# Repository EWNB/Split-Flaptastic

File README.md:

# Split-Flaptastic
Various files for making Split-Flap displays

# Files
* Circ/
  * Contains attempts and various circuit designs. [Here are lions](https://en.wikipedia.org/wiki/Here_be_dragons).
* Code/
  * Here lives embedded code for running split-flap devices or parts thereof.
  * RegFlap/ 
    * New Arduino shift register controlled split-flap display program.
  * RegSpinCTRL/
    * Old Arduino shift register controlled split-flap display program.
  * RegSpinFlap/
    * Arduino shift register controlled motor spinner for testing hardware.
* Flaps/
  * Within lies a script most reptilian that creates flap template PDFs.

# Blog
I write about this project on my blog. Search engines don't seem to know that it exists, so here's a link:
https://transistorized-tui.blogspot.com/search/label/Split-Flaptastic
These files on GitHub will likely be ahead of the narative on the blog, as I'm lazy and often prefer to advance the project than bother letting anybody know about it.

# Licence
Not sure yet...

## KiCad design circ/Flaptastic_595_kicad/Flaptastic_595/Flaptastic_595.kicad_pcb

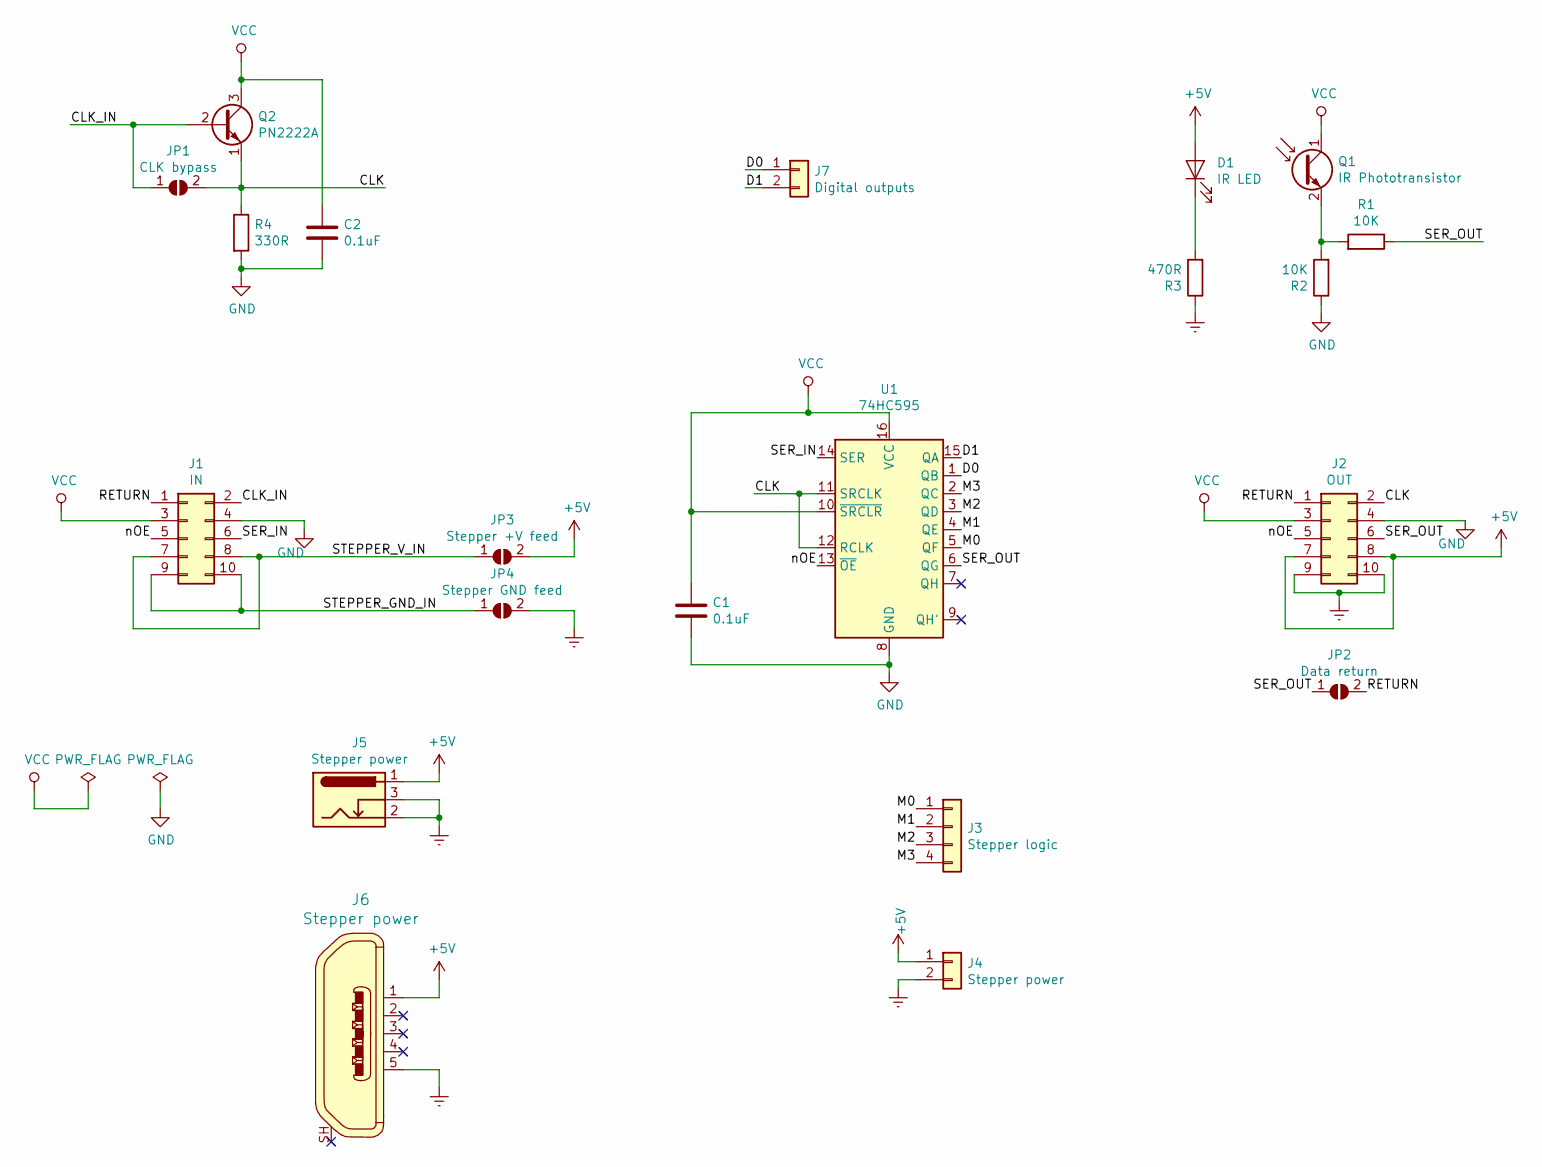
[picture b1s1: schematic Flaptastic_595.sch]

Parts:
C1, C2: 0.1uF; CAP-PTH-2.54
D1: IR LED; LED_D5.0mm_Clear
J1: IN; IDC-Header_2x05_P2.54mm_Vertical
J2: OUT; IDC-Header_2x05_P2.54mm_Vertical
J3: Stepper logic; PinHeader_1x04_P2.54mm_Vertical
J4: Stepper power; PinHeader_1x02_P2.54mm_Vertical
J5: Stepper power; BarrelJack_CUI_PJ-102AH_Horizontal
J6: Stepper power; USB_Micro_B_Female_10118194-0001LF; MPN 10118194-0001LF; Digi-Key_PN 609-4618-1-ND
J7: Digital outputs; PinHeader_1x02_P2.54mm_Vertical
JP1: CLK bypass; SolderJumper-2_P1.3mm_Open_RoundedPad1.0x1.5mm
JP2: Data return; SolderJumper-2_P1.3mm_Open_RoundedPad1.0x1.5mm
JP3: Stepper +V feed; SolderJumper-2_P1.3mm_Open_RoundedPad1.0x1.5mm
JP4: Stepper GND feed; SolderJumper-2_P1.3mm_Open_RoundedPad1.0x1.5mm
Q1: IR Phototransistor; LED_D5.0mm_IRBlack
Q2: PN2222A; TO-92_Inline
R1, R2: 10K; R_Axial_DIN0204_L3.6mm_D1.6mm_P7.62mm_Horizontal
R3: 470R; R_Axial_DIN0204_L3.6mm_D1.6mm_P7.62mm_Horizontal
R4: 330R; R_Axial_DIN0204_L3.6mm_D1.6mm_P7.62mm_Horizontal
U1: 74HC595; DIP-16_W7.62mm

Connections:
+5V: D1.2 (A), J2.7, J2.8, J4.1, J5.1, J6.1, JP3.2 (B)
/CLK: J2.2, JP1.2 (B), Q2.1 (E), R4.1, U1.11 (SRCLK), U1.12 (RCLK)
/CLK_IN: J1.2, JP1.1 (A), Q2.2 (B)
/D0: J7.1, U1.1 (QB)
/D1: J7.2, U1.15 (QA)
/M0: J3.1, U1.5 (QF)
/M1: J3.2, U1.4 (QE)
/M2: J3.3, U1.3 (QD)
/M3: J3.4, U1.2 (QC)
/RETURN: J1.1, J2.1, JP2.2 (B)
/SER_IN: J1.6, U1.14 (SER)
/SER_OUT: J2.6, JP2.1 (A), R1.1, U1.6 (QG)
/STEPPER_GND_IN: J1.9, J1.10, JP4.1 (A)
/STEPPER_V_IN: J1.7, J1.8, JP3.1 (A)
/nOE: J1.5, J2.5, U1.13 (~OE)
Earth: J2.9, J2.10, J4.2, J5.2, J5.3, J6.5, JP4.2 (B), R3.1
GND: C1.2, C2.2, J1.4, J2.4, R2.1, R4.2, U1.8 (GND)
unnamed: D1.1 (K), R3.2
unnamed: Q1.2 (E), R1.2, R2.2
VCC: C1.1, C2.1, J1.3, J2.3, Q1.1 (C), Q2.3 (C), U1.10 (~SRCLR), U1.16 (VCC)

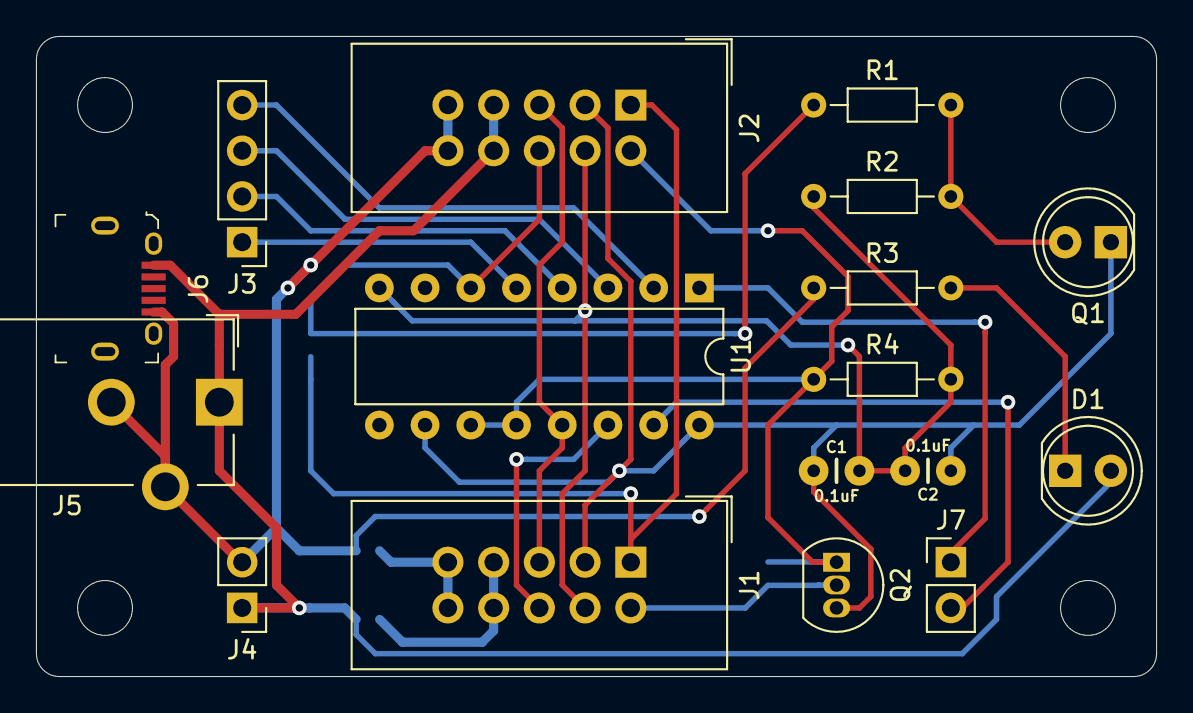
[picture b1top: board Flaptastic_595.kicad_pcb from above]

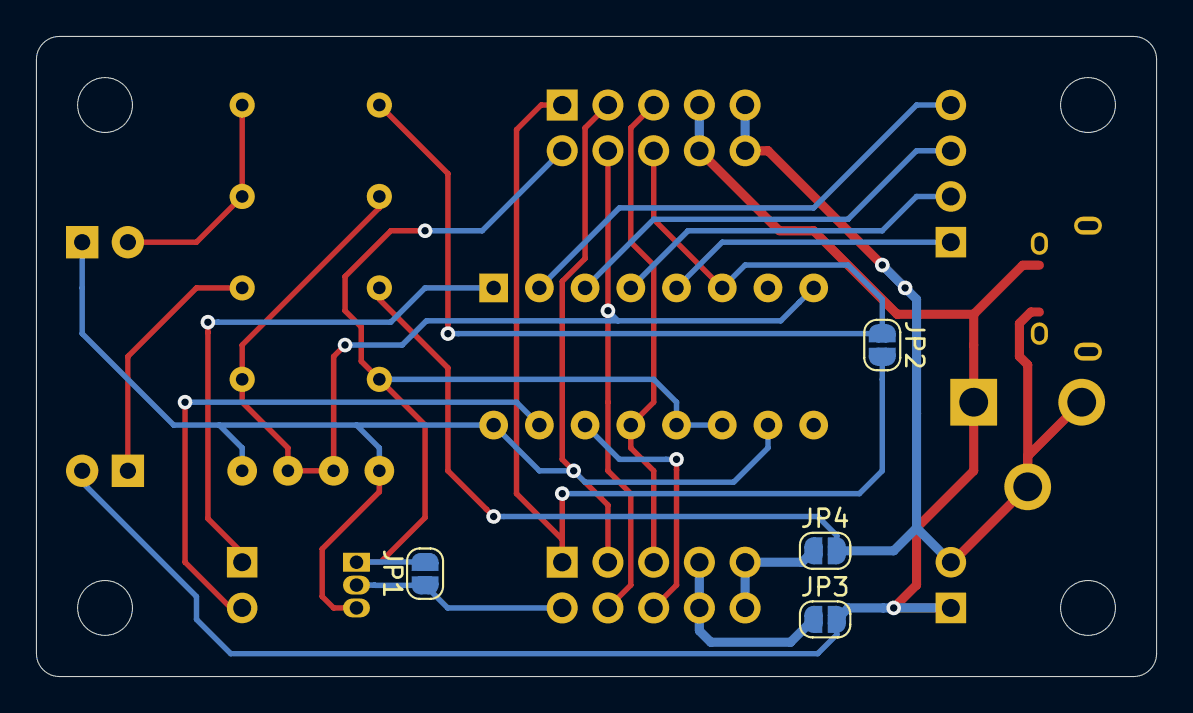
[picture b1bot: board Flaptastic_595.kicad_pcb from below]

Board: 2 copper layers, 62.2 x 35.6 mm, 21 parts (4 on the bottom side), 20 nets.

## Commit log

2019-04-13 Interrupt timing and semi-functional target setting
2019-04-13 Parameterised loop flap incrementation
2019-04-13 Fixed target find, homes every rev
2019-04-13 Home offset, setTargets(), reachedTarget[s]()
2019-04-13 Got flaps.py to draw blank flaps
2019-04-13 Nice messages, loop change
2019-04-13 [flaps] Add initial pycairo script
2019-04-13 Modified RegSpinFlap for 194 system
2019-04-13 End of 299 development
2019-04-13 Made flaps.py able to place graphics from inkscape file onto flaps, Multiple pages of flaps
2019-04-13 [code] Make demo go through all flaps, make unprintable characters ' ' again
2019-04-13 [circ] Fritzing 595 circ start
2019-04-13 Got flaps.py able to do vectorised text, got RegSpinCTRL working with new electroincs
2019-04-13 [flaps] Swap mistakenly committed .pdf for .py src
2019-04-13 Add demo mode
2019-04-13 Change line endings to LF
2019-04-13 Reduce .gitignore to pdfs and Flaps/tmp
2019-04-14 Update README with file description and blog link
2019-04-14 [Code] Move code projects into Code/ directory
2019-04-14 Add .svg to .gitignore
2019-04-16 [code] 595 shift reg update
2019-04-16 [circ] Reduce to one 595 circuit, tweaks from getting it running
2019-05-28 [tidy] Lower case directory names
2019-06-11 [code] Multi-unit display initial testing
2019-06-13 [circ] Add cap to logic power
2019-06-13 [code] Tried to change line endings to LF
2019-06-13 [code] Started on control code rewrite
2019-06-16 [code] Completed untested draft of Flaptastic library
2019-06-18 [code] Got Flaptastic lib working, improved demo program, performance tweaks
2019-06-22 [code] Add bidirectional logic (untested), change usage of 'byte' type to uint8_t
2019-06-22 [code] Only home if going forwards
2019-08-06 Draft PCB in KiCAD
2019-08-13 [code] Del bi,shift,en. Add flashing outs, and int disable
2019-08-20 Worked on PCB, rm bak files
2019-08-20 Ignore KiCad temp files
2019-09-24 Draft laser cut designs
2019-09-24 Stop ignoring .svg files
2019-10-01 Worked on wheel for laser cut
2019-10-01 Add Arduino Makefile
2019-10-08 Refined laser-cut designs
2019-10-15 Further laser-cut improvements
2019-10-22 Modify flaps.py for 40 flap alphanum
2021-09-23 Trim RegFlap to hex unit only
2021-10-07 Draft smaller wheel and frame
2022-02-01 Tidy flaps.py
2022-02-08 Tweak cad designs after prototype
2022-02-22 Add cad doc, flaps.py classes
2022-03-08 WIP calculate frame size
2022-03-15 Refined frame calculations and design
2022-03-22 Tweak frame some more
2022-04-12 Further flaps.py refinements
    Added shebang, module docstring, more default args, added unicode
    symbols to the example, removed old 'space' flap insertion, added
    comments, added check of provided image paths.
2022-04-26 Tweak flaps generated, include PDF example
2022-05-24 Update frame calc, part-update svg
2022-06-07 Started on frame diagram
2022-06-07 Add TODO
2022-08-02 Further developed helpful diagram
